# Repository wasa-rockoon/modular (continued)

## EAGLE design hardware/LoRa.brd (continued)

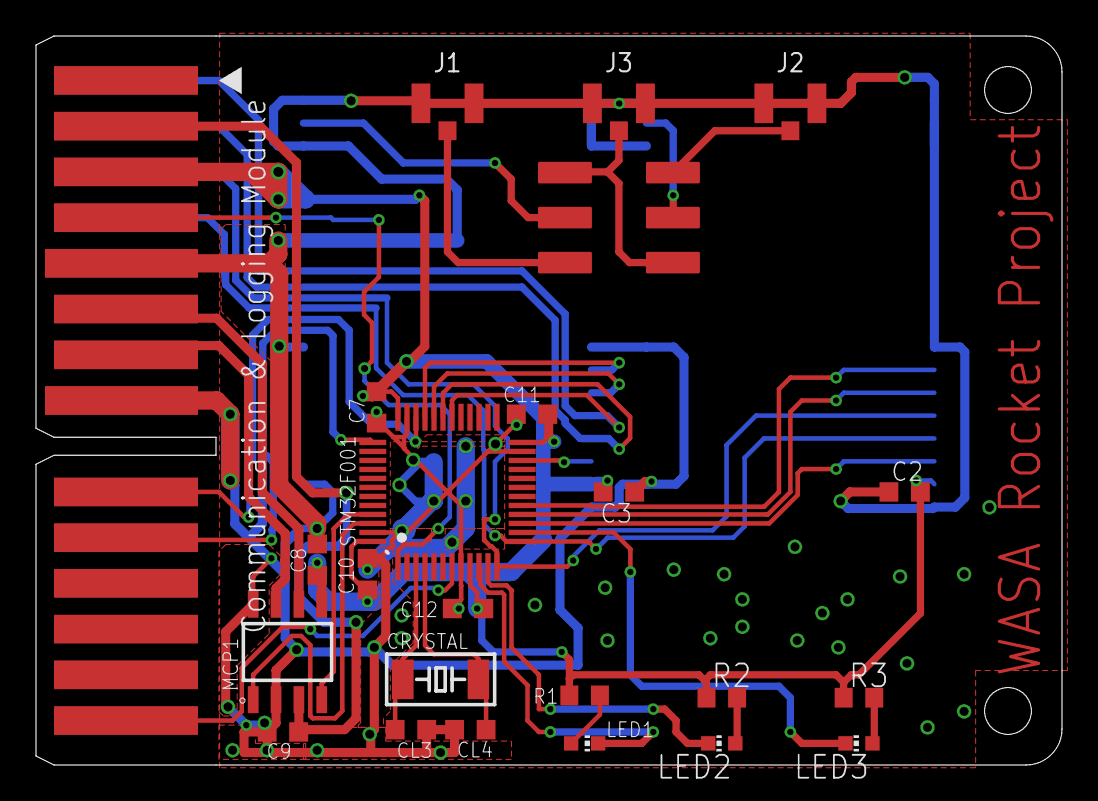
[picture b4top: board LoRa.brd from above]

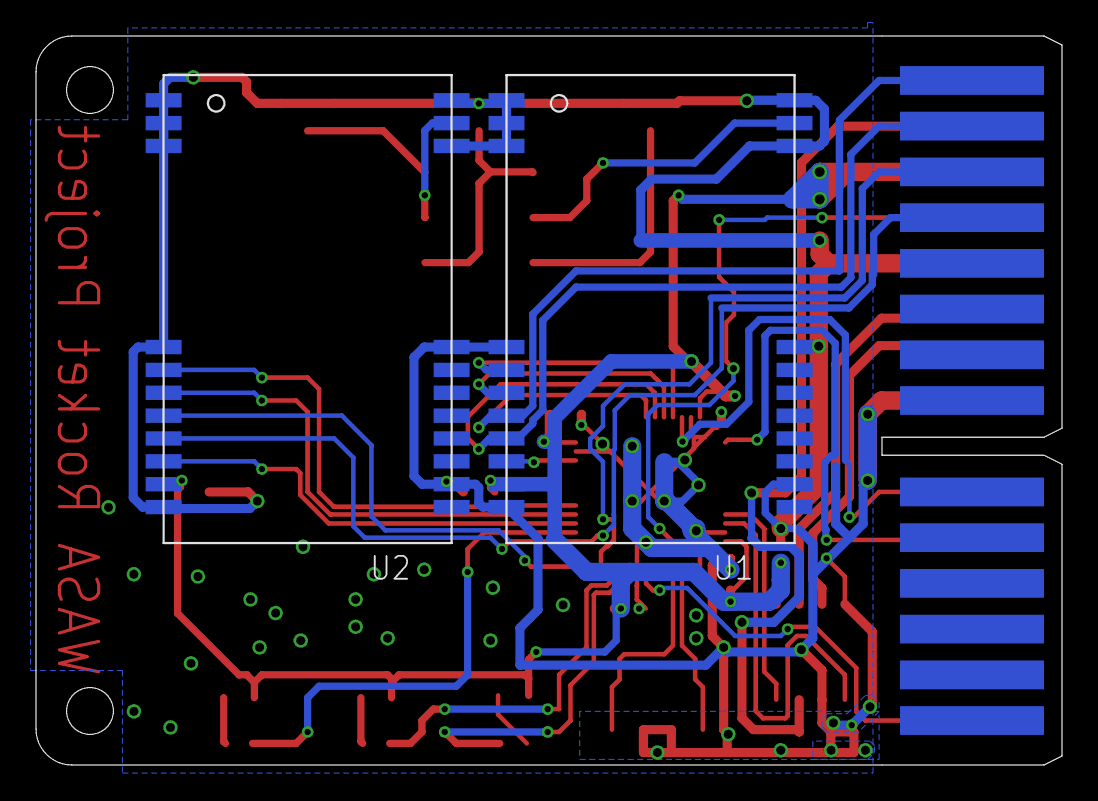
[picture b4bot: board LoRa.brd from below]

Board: 2 copper layers, 57.0 x 40.5 mm, 26 parts (2 on the bottom side), 34 nets.

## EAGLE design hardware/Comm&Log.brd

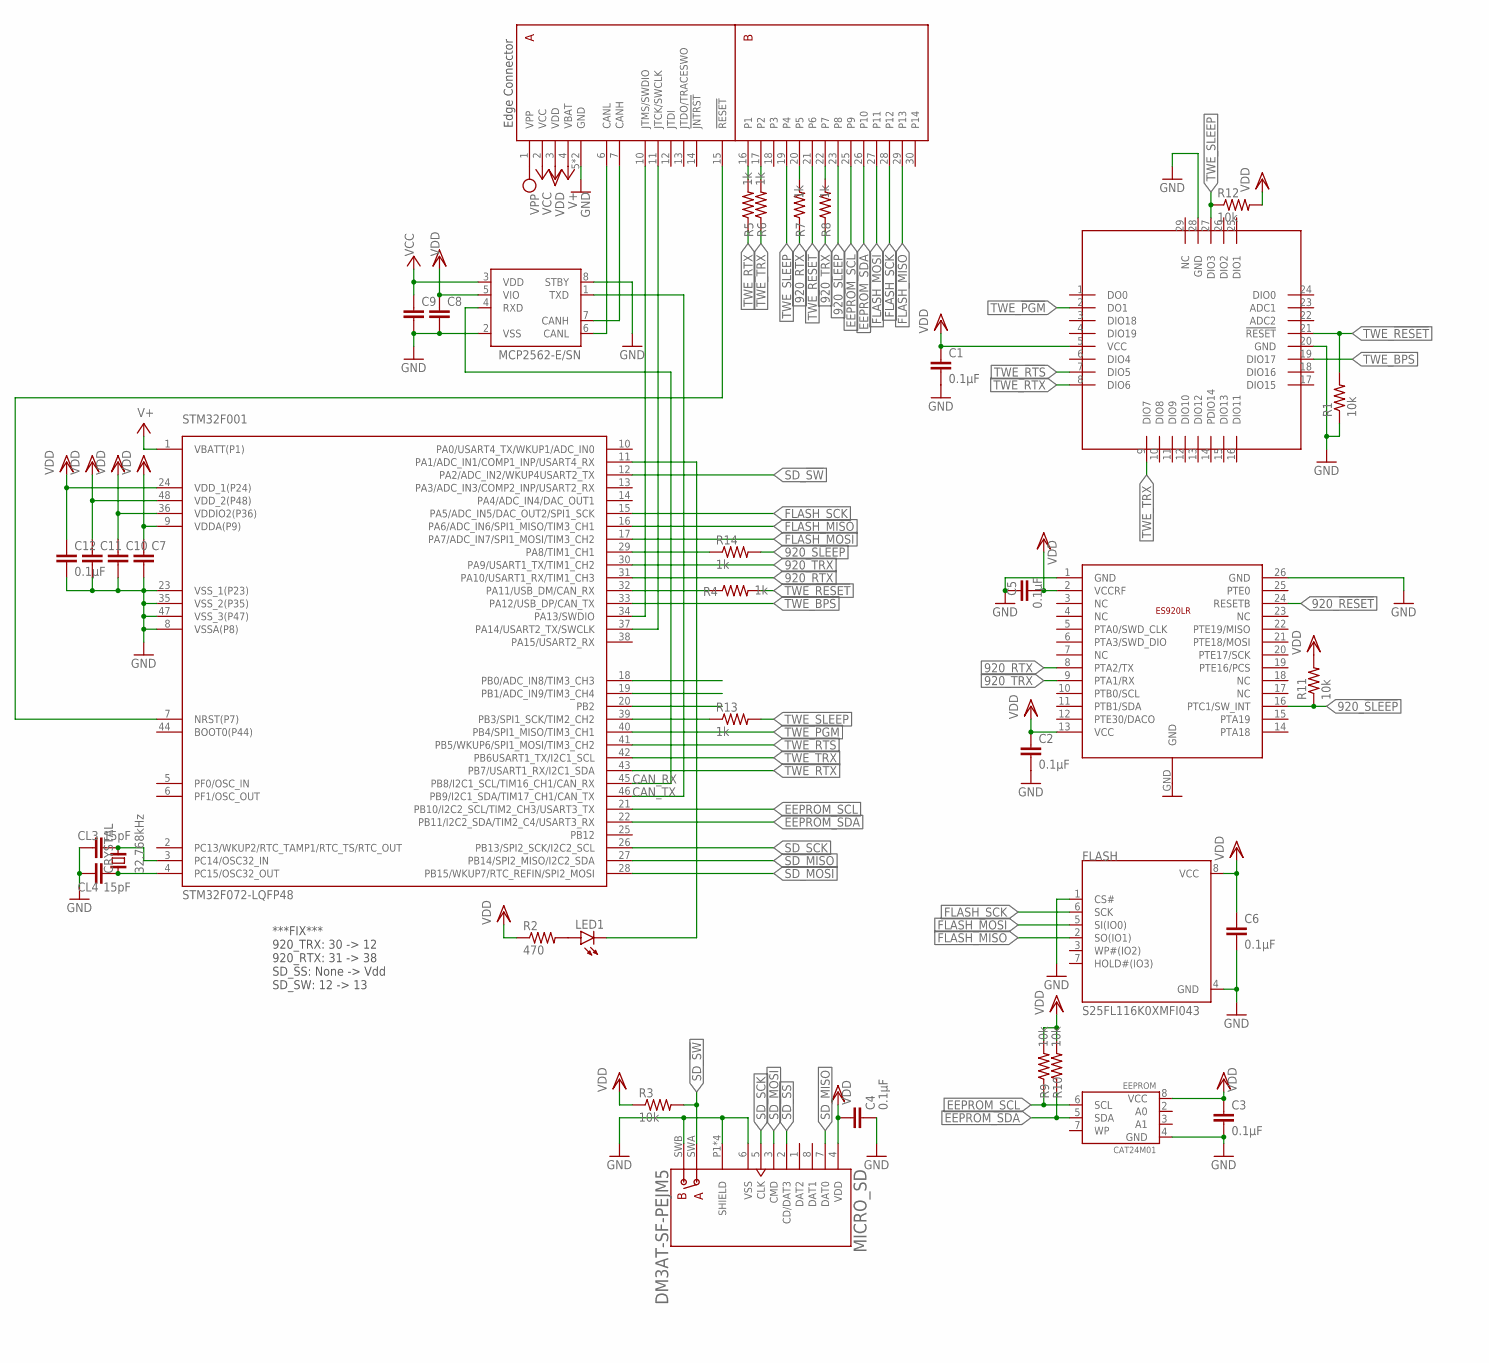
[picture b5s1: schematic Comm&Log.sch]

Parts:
C1, C2, C3, C4, C5, C6, C12: 0.1µF; C0603K
C7, C8, C9, C10, C11: C-EUC0603K; C0603K
CL3, CL4: 15pF; C0603K
CRYSTAL: 32.768kHz; FC-255
EEPROM: CAT24M01; SO-8
ES920LR: ES920LR
FLASH: S25FL116K0XMFI043; SOIC127P600X175-8N
LED1: LEDCHIP-LED0603; CHIP-LED0603
MCP1: MCP2562-E/SN; SOIC127P600X175-8N
MICRO_SD: DM3AT-SF-PEJM5; HRS_DM3AT-SF-PEJM5
R1, R3, R9, R10, R11, R12: 10k; R0603
R2: 470; R0603
R4, R5, R6, R7, R8, R13, R14: 1k; R0603
STM32F001: STM32F072-LQFP48; LQFP48
TWE-LITE: LITE
U$2: EDGE30

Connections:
920_!RESET!: ES920LR.24 (RESETB)
920_!SLEEP!: ES920LR.16 (PTC1/SW_INT), R11.1, R14.2, U$2.23 (P8)
920_!SLEEP!': R14.1, STM32F001.29 (PA8/TIM1_CH1)
920_RTX: ES920LR.8 (PTA2/TX), R7.1, STM32F001.31 (PA10/USART1_RX/TIM1_CH3)
920_RTX_: R7.2, U$2.20 (P5)
920_TRX: ES920LR.9 (PTA1/RX), R8.1, STM32F001.30 (PA9/USART1_TX/TIM1_CH2)
920_TRX_: R8.2, U$2.22 (P7)
CANH1: MCP1.7 (CANH), U$2.7 (CANH)
CANL1: MCP1.6 (CANL), U$2.6 (CANL)
CAN_RX: MCP1.4 (RXD), STM32F001.45 (PB8/I2C1_SCL/TIM16_CH1/CAN_RX)
CAN_TX: MCP1.1 (TXD), STM32F001.46 (PB9/I2C1_SDA/TIM17_CH1/CAN_TX)
EEPROM_SCL: EEPROM.6 (SCL), R9.1, STM32F001.21 (PB10/I2C2_SCL/TIM2_CH3/USART3_TX), U$2.25 (P9)
EEPROM_SDA: EEPROM.5 (SDA), R10.1, STM32F001.22 (PB11/I2C2_SDA/TIM2_C4/USART3_RX), U$2.26 (P10)
FLASH_MISO: FLASH.2 (SO(IO1)), STM32F001.16 (PA6/ADC_IN6/SPI1_MISO/TIM3_CH1), U$2.29 (P13)
FLASH_MOSI: FLASH.5 (SI(IO0)), STM32F001.17 (PA7/ADC_IN7/SPI1_MOSI/TIM3_CH2), U$2.27 (P11)
FLASH_SCK: FLASH.6 (SCK), STM32F001.15 (PA5/ADC_IN5/DAC_OUT2/SPI1_SCK), U$2.28 (P12)
GND: C1.2, C2.2, C3.2, C4.2, C5.1, C6.2, C7.2, C8.2, C9.2, C10.2, C11.2, C12.2, CL3.1, CL4.1, EEPROM.4 (GND), ES920LR.1 (GND), ES920LR.26 (GND), ES920LR.GND, FLASH.1 (CS#), FLASH.4 (GND), MCP1.2 (VSS), MCP1.8 (STBY), MICRO_SD.6 (VSS), MICRO_SD.P1 (SHIELD), MICRO_SD.P2 (SHIELD), MICRO_SD.P3 (SHIELD), MICRO_SD.P4 (SHIELD), MICRO_SD.SWB (B), R1.1, STM32F001.8 (VSSA(P8)), STM32F001.23 (VSS_1(P23)), STM32F001.35 (VSS_2(P35)), STM32F001.47 (VSS_3(P47)), TWE-LITE.20 (GND), TWE-LITE.28 (GND), U$2.5 (GND), U$2.8 (GND)
unnamed: R4.1, STM32F001.32 (PA11/USB_DM/CAN_RX)
unnamed: R6.2, U$2.17 (P2)
unnamed: R13.1, STM32F001.39 (PB3/SPI1_SCK/TIM2_CH2)
unnamed: CL4.2, CRYSTAL.1, STM32F001.4 (PC15/OSC32_OUT)
unnamed: CL3.2, CRYSTAL.2, STM32F001.3 (PC14/OSC32_IN)
unnamed: LED1.C, STM32F001.11 (PA1/ADC_IN1/COMP1_INP/USART4_RX)
unnamed: R5.2, U$2.16 (P1)
unnamed: LED1.A, R2.2
NRST1: STM32F001.7 (NRST(P7)), U$2.15 (!RESET!)
SD_!SS!: MICRO_SD.2 (CD/DAT3)
SD_!SW!: MICRO_SD.SWA (A), R3.2, STM32F001.12 (PA2/ADC_IN2/WKUP4USART2_TX)
SD_MISO: MICRO_SD.7 (DAT0), STM32F001.27 (PB14/SPI2_MISO/I2C2_SDA)
SD_MOSI: MICRO_SD.3 (CMD), STM32F001.28 (PB15/WKUP7/RTC_REFIN/SPI2_MOSI)
SD_SCK: MICRO_SD.5 (CLK), STM32F001.26 (PB13/SPI2_SCK/I2C2_SCL)
SWCLK1: STM32F001.37 (PA14/USART2_TX/SWCLK), U$2.11 (JTCK/SWCLK)
SWDIO1: STM32F001.34 (PA13/SWDIO), U$2.10 (JTMS/SWDIO)
TWE_!PGM!: STM32F001.40 (PB4/SPI1_MISO/TIM3_CH1), TWE-LITE.2 (DO1)
TWE_!RESET!: R1.2, R4.2, TWE-LITE.21 (!RESET!), U$2.21 (P6)
TWE_!RTS!: STM32F001.41 (PB5/WKUP6/SPI1_MOSI/TIM3_CH2), TWE-LITE.7 (DIO5)
TWE_BPS: STM32F001.33 (PA12/USB_DP/CAN_TX), TWE-LITE.19 (DIO17)
TWE_RTX: R5.1, STM32F001.43 (PB7/USART1_RX/I2C1_SDA), TWE-LITE.8 (DIO6)
TWE_SLEEP: R12.1, R13.2, TWE-LITE.27 (DIO3), U$2.19 (P4)
TWE_TRX: R6.1, STM32F001.42 (PB6USART1_TX/I2C1_SCL), TWE-LITE.9 (DIO7)
VBAT: STM32F001.1 (VBATT(P1)), U$2.4 (VBAT)
VCC: C9.1, MCP1.3 (VDD), U$2.2 (VCC)
VDD: C1.1, C2.1, C3.1, C4.1, C5.2, C6.1, C7.1, C8.1, C10.1, C11.1, C12.1, EEPROM.8 (VCC), ES920LR.2 (VCCRF), ES920LR.13 (VCC), FLASH.8 (VCC), MCP1.5 (VIO), MICRO_SD.4 (VDD), R2.1, R3.1, R9.2, R10.2, R11.2, R12.2, STM32F001.9 (VDDA(P9)), STM32F001.24 (VDD_1(P24)), STM32F001.36 (VDDIO2(P36)), STM32F001.48 (VDD_2(P48)), TWE-LITE.5 (VCC), U$2.3 (VDD)
VPP: U$2.1 (VPP)

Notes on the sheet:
***FIX*** 920_TRX: 30 -> 12 920_RTX: 31 -> 38 SD_SS: None -> Vdd SD_SW: 12 -> 13

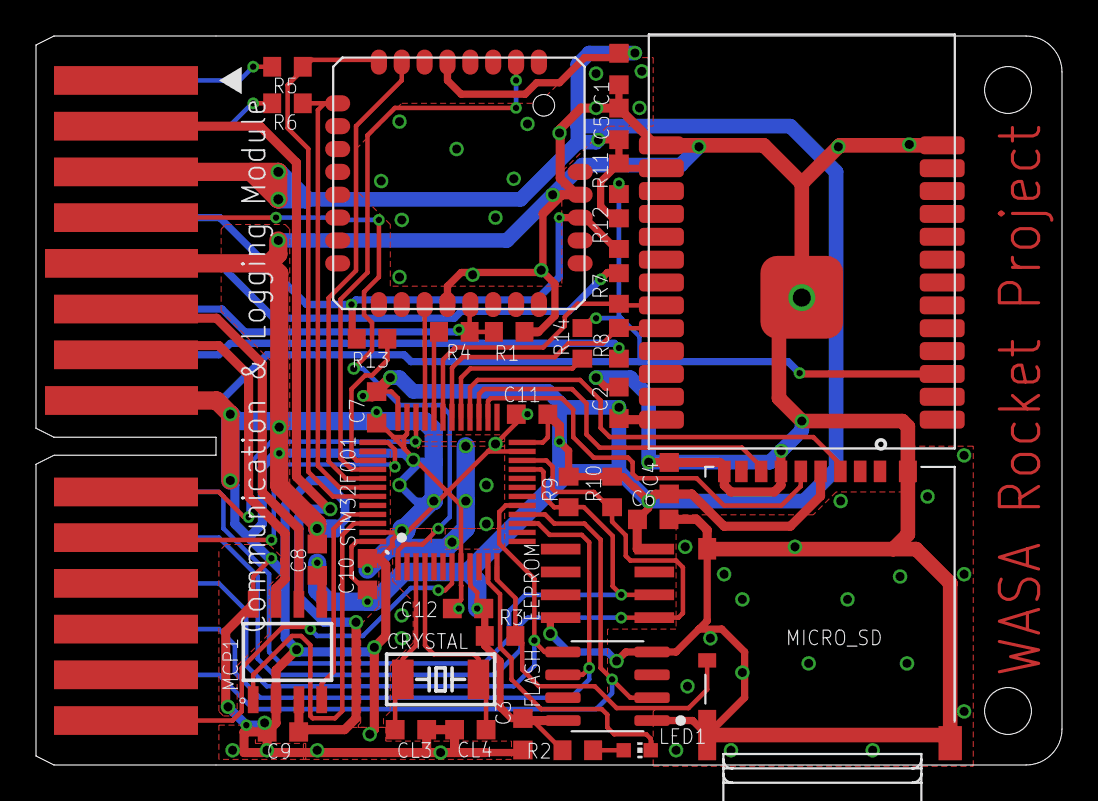
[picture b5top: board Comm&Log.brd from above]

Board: 2 copper layers, 57.0 x 40.5 mm, 38 parts (0 on the bottom side), 41 nets.

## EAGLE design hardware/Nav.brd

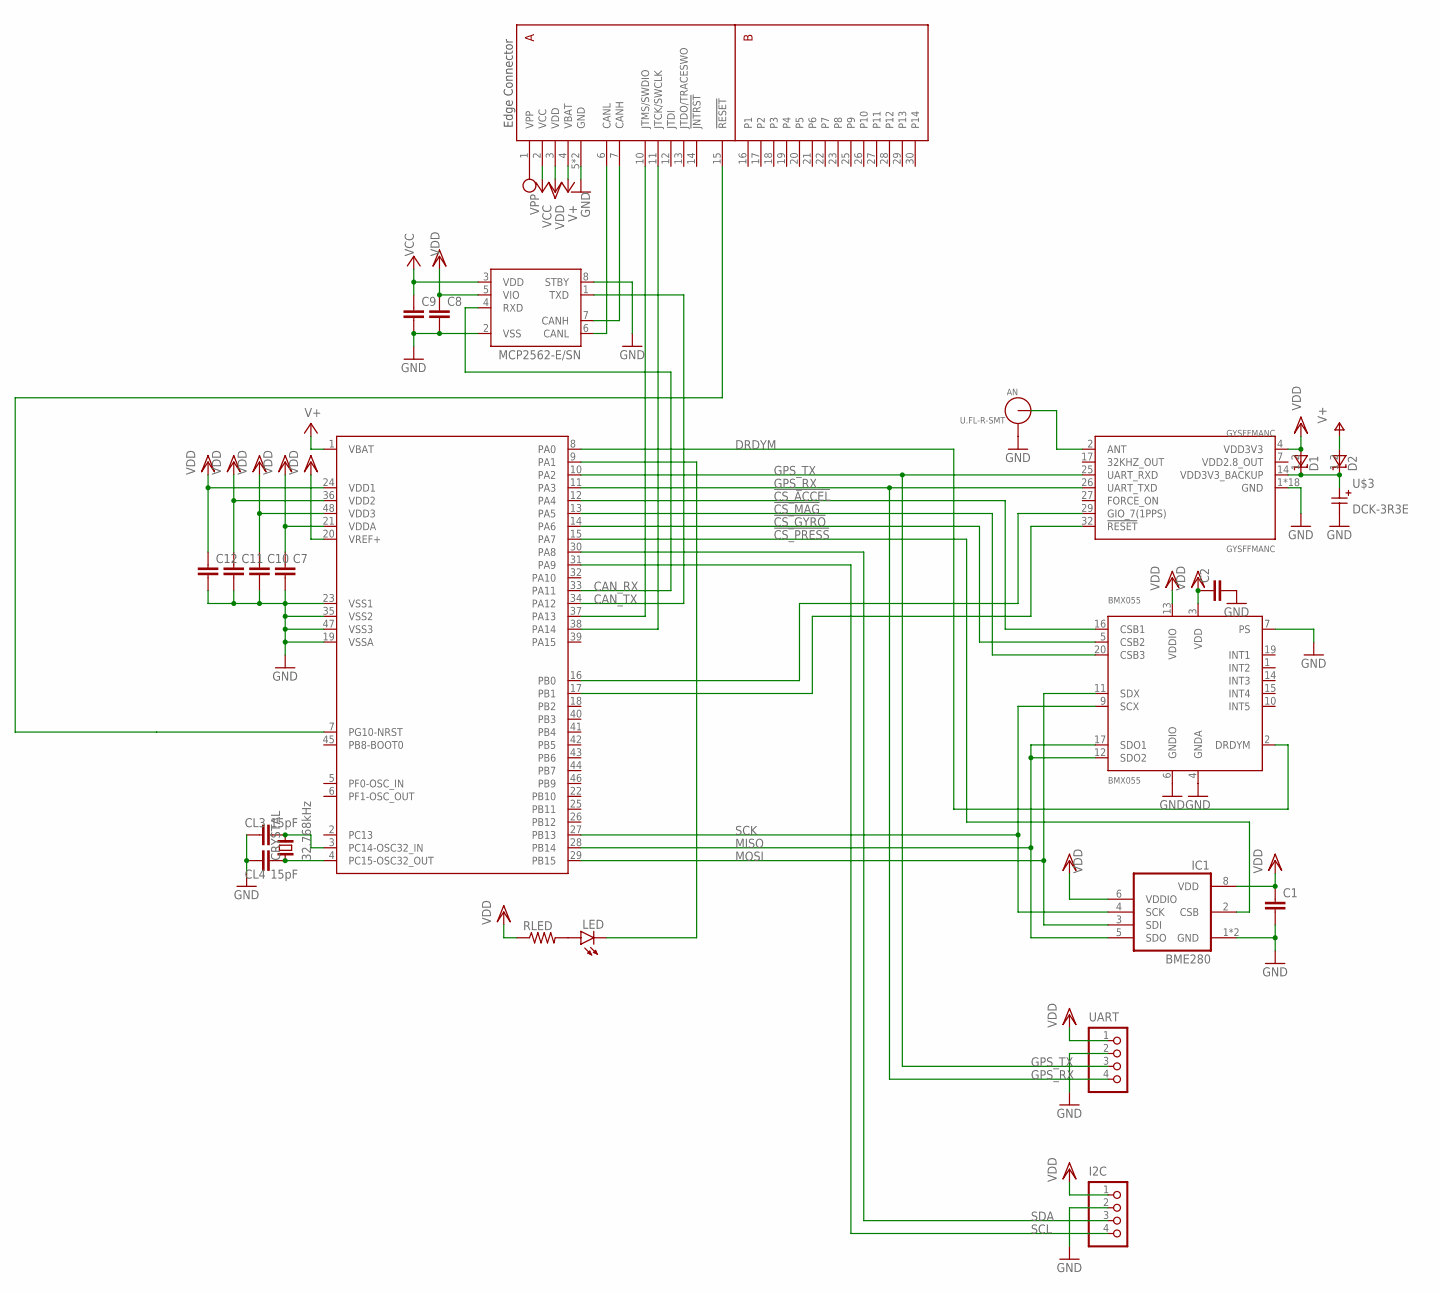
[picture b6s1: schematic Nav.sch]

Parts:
AN: U.FL-R-SMT; U.FL_SMT
BMX055: BMX055
C1, C2, C7, C8, C9, C10, C11, C12: C-EUC0603K; C0603K
CL3, CL4: 15pF; C0603K
CRYSTAL: 32.768kHz; FC-255
D1, D2: RB521S-30TE61; SODFL1608X70N
GYSFFMANC: GYSFFMANC
I2C: S4B-PH-K-S
IC1: BME280
LED: LEDCHIP-LED0603; CHIP-LED0603
MCP2562: MCP2562-E/SN; SOIC127P600X175-8N
RLED: R-US_R0603; R0603
U$1: STM32G431-LQFP48; LQFP48
U$2: EDGE30
U$3: DCK-3R3E; DC,DCK
UART: S4B-PH-K-S

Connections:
!CS_ACCEL!: BMX055.16 (CSB1), U$1.12 (PA4)
!CS_GYRO!: BMX055.5 (CSB2), U$1.14 (PA6)
!CS_MAG!: BMX055.20 (CSB3), U$1.13 (PA5)
!CS_PRESS!: IC1.2 (CSB), U$1.15 (PA7)
CANH1: MCP2562.7 (CANH), U$2.7 (CANH)
CANL1: MCP2562.6 (CANL), U$2.6 (CANL)
CAN_RX: MCP2562.4 (RXD), U$1.33 (PA11)
CAN_TX: MCP2562.1 (TXD), U$1.34 (PA12)
DRDYM: BMX055.2 (DRDYM), U$1.8 (PA0)
GND: AN.GND1, AN.GND2, BMX055.4 (GNDA), BMX055.6 (GNDIO), BMX055.7 (PS), C1.2, C2.2, C7.2, C8.2, C9.2, C10.2, C11.2, C12.2, CL3.1, CL4.1, GYSFFMANC.1 (GND), GYSFFMANC.3 (GND), GYSFFMANC.8 (GND), GYSFFMANC.10 (GND), GYSFFMANC.12 (GND), GYSFFMANC.22 (GND), GYSFFMANC.33 (GND), GYSFFMANC.36 (GND), GYSFFMANC.37 (GND), GYSFFMANC.38 (GND), GYSFFMANC.39 (GND), GYSFFMANC.40 (GND), GYSFFMANC.41 (GND), GYSFFMANC.42 (GND), GYSFFMANC.43 (GND), GYSFFMANC.44 (GND), GYSFFMANC.45 (GND), GYSFFMANC.46 (GND), I2C.2, IC1.1 (GND), IC1.7 (GND), MCP2562.2 (VSS), MCP2562.8 (STBY), U$1.19 (VSSA), U$1.23 (VSS1), U$1.35 (VSS2), U$1.47 (VSS3), U$2.5 (GND), U$2.8 (GND), U$3.-, UART.2
GPS_RX: GYSFFMANC.26 (UART_TXD), U$1.11 (PA3), UART.4
GPS_TX: GYSFFMANC.25 (UART_RXD), U$1.10 (PA2), UART.3
MISO: BMX055.12 (SDO2), BMX055.17 (SDO1), IC1.5 (SDO), U$1.28 (PB14)
MOSI: BMX055.11 (SDX), IC1.3 (SDI), U$1.29 (PB15)
unnamed: AN.SIG (ANT), GYSFFMANC.2 (ANT)
unnamed: GYSFFMANC.29 (GIO_7(1PPS)), U$1.16 (PB0)
unnamed: GYSFFMANC.32 (!RESET!), U$1.17 (PB1)
unnamed: U$1.7 (PG10-NRST), U$2.15 (!RESET!)
unnamed: LED.C, U$1.9 (PA1)
unnamed: CL4.2, CRYSTAL.1, U$1.4 (PC15-OSC32_OUT)
unnamed: CL3.2, CRYSTAL.2, U$1.3 (PC14-OSC32_IN)
unnamed: LED.A, RLED.2
SCK: BMX055.9 (SCX), IC1.4 (SCK), U$1.27 (PB13)
SCL: I2C.4, U$1.31 (PA9)
SDA: I2C.3, U$1.30 (PA8)
SWCLK1: U$1.38 (PA14), U$2.11 (JTCK/SWCLK)
SWDIO1: U$1.37 (PA13), U$2.10 (JTMS/SWDIO)
VBACKUP: D1.1 (K), D2.1 (K), GYSFFMANC.14 (VDD3V3_BACKUP), U$3.+
VBAT: D2.2 (A), U$1.1 (VBAT), U$2.4 (VBAT)
VCC: C9.1, MCP2562.3 (VDD), U$2.2 (VCC)
VDD: BMX055.3 (VDD), BMX055.13 (VDDIO), C1.1, C2.1, C7.1, C8.1, C10.1, C11.1, C12.1, D1.2 (A), GYSFFMANC.4 (VDD3V3), I2C.1, IC1.6 (VDDIO), IC1.8 (VDD), MCP2562.5 (VIO), RLED.1, U$1.20 (VREF+), U$1.21 (VDDA), U$1.24 (VDD1), U$1.36 (VDD2), U$1.48 (VDD3), U$2.3 (VDD), UART.1
VDD2.8_OUT: GYSFFMANC.7 (VDD2.8_OUT)
VPP: U$2.1 (VPP)

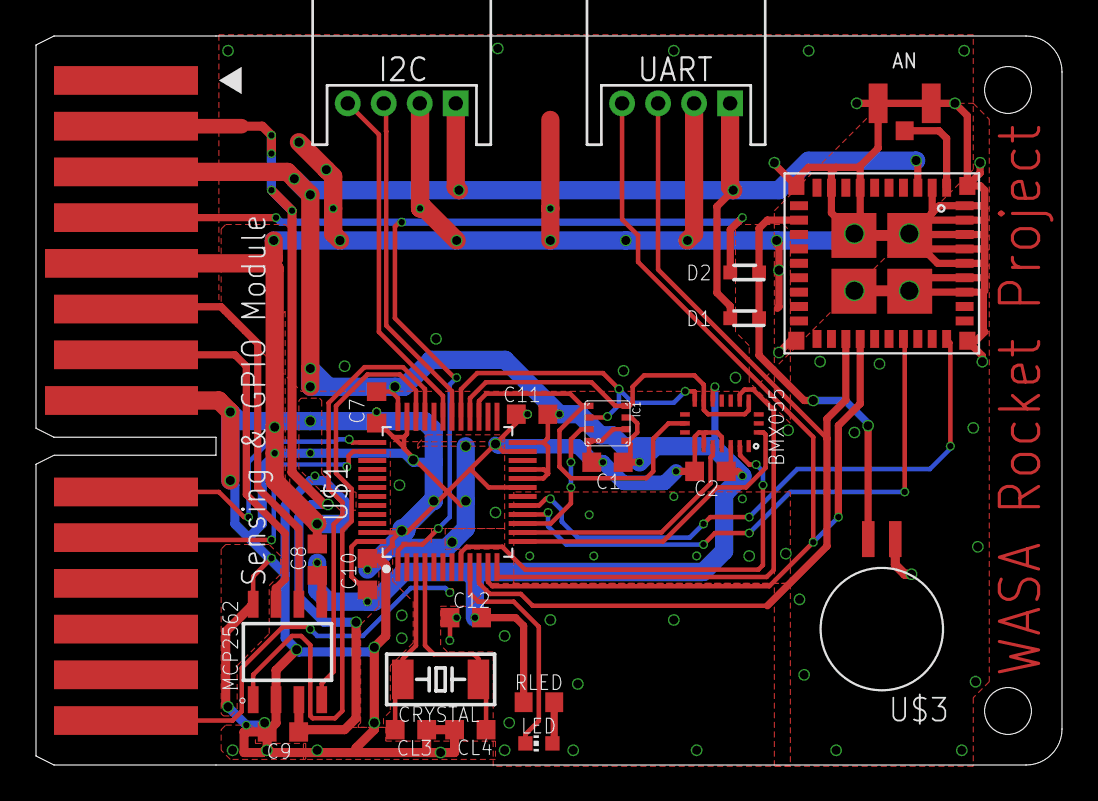
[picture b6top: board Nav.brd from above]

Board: 2 copper layers, 57.0 x 40.5 mm, 25 parts (0 on the bottom side), 31 nets.

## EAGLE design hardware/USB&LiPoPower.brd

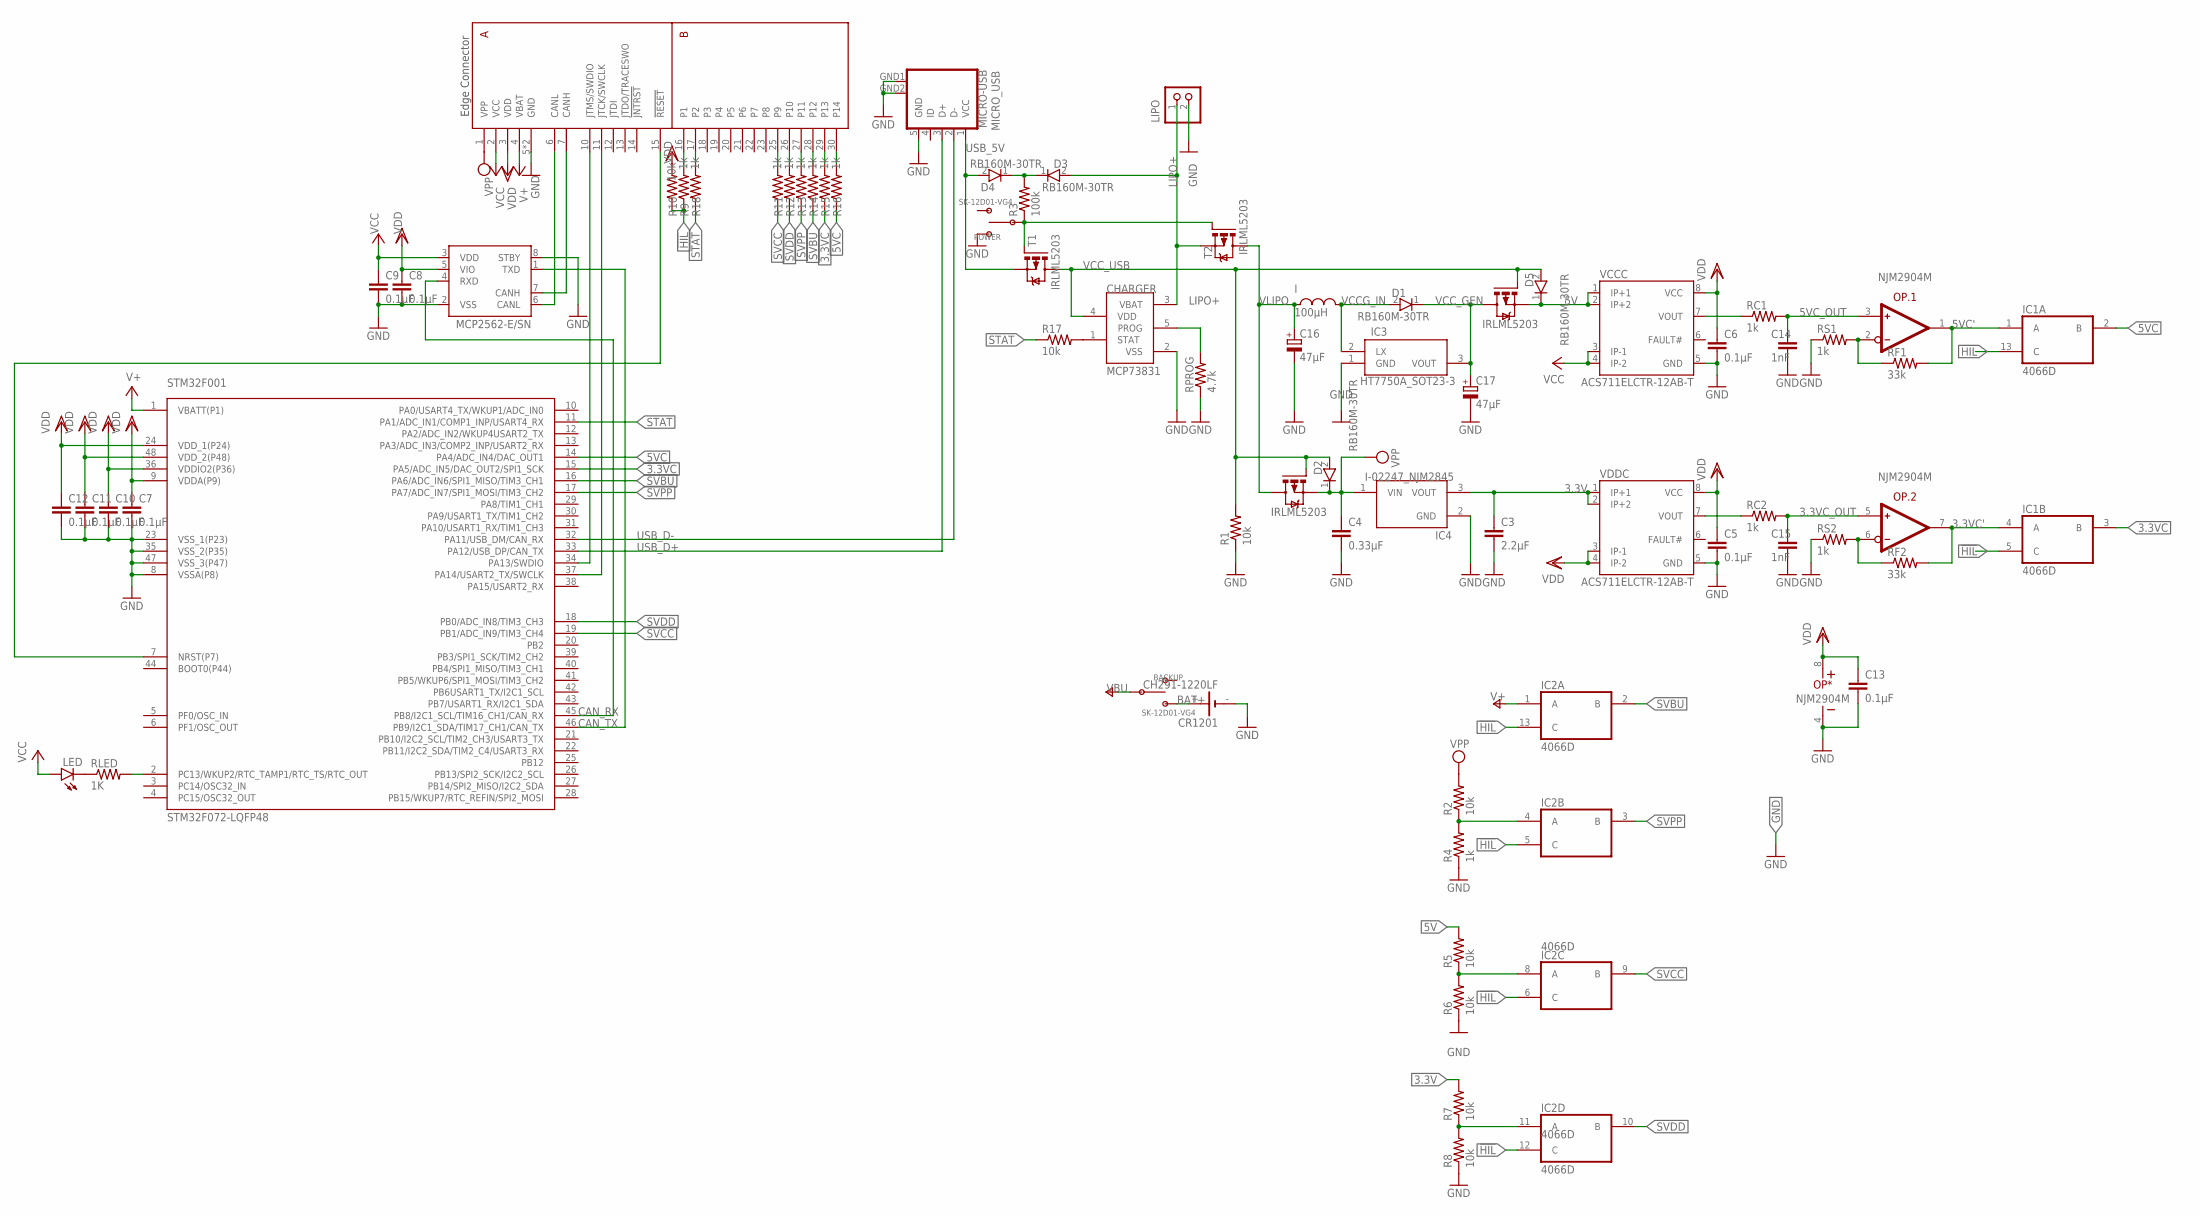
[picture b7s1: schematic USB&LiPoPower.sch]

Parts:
BACKUP: SK-12D01-VG4
C3: 2.2µF; C0603K
C4: 0.33µF; C0603K
C5, C6, C7, C8, C9, C10, C11, C12, C13: 0.1µF; C0603K
C14, C15: 1nF; C0603K
C16, C17: 47µF; UD-5X5,8_NICHICON
CHARGER: MCP73831; SOT23-5L
CR1201: CH291-1220LF
D1, D2, D3, D4, D5: RB160M-30TR; SODFL3516X90N
I: 100µH; NR10050
IC1, IC2: 4066D; SO14
IC3: HT7750A_SOT23-3; SOT95P190X145-3N
IC4: I-02247_NJM2845; TO252
LED: LEDCHIP-LED0603; CHIP-LED0603
LIPO: S2B-PH-K-S
MCP2562: MCP2562-E/SN; SOIC127P600X175-8N
MICRO_USB: MICRO-USB
OP: NJM2904M; SO-8
POWER: SK-12D01-VG4
R1, R2, R5, R6, R7, R8, R10, R17: 10k; R0603
R3: 100k; R0603
R4, R9, R11, R12, R13, R14, R15, R16, R18: 1k; R0603
RC1, RC2: 1k; R0603
RF1, RF2: 33k; R0603
RLED: 1K; R0603
RPROG: 4.7k; R0603
RS1, RS2: 1k; R0603
STM32F001: STM32F072-LQFP48; LQFP48
T1, T2, T3, T4: IRLML5203; MICRO3
U$2: EDGE30
VCCC: ACS711ELCTR-12AB-T; SOIC8
VDDC: ACS711ELCTR-12AB-T; SOIC8

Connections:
3.3V: C3.1, IC4.3 (VOUT), R7.2, VDDC.1 (IP+1), VDDC.2 (IP+2)
3.3VC: IC1.3 (B), R15.1, STM32F001.15 (PA5/ADC_IN5/DAC_OUT2/SPI1_SCK)
3.3VC': IC1.4 (A), OP.7 (OUT), RF2.2
3.3VC_OUT: C15.1, OP.5 (IN+), RC2.2
3.3VC_OUT': RC2.1, VDDC.7 (VOUT)
5V: D5.1 (K), R5.2, T3.2 (S), VCCC.1 (IP+1), VCCC.2 (IP+2)
5VC: IC1.2 (B), R16.1, STM32F001.14 (PA4/ADC_IN4/DAC_OUT1)
5VC': IC1.1 (A), OP.1 (OUT), RF1.2
5VC_OUT: C14.1, OP.3 (IN+), RC1.2
5VC_OUT': RC1.1, VCCC.7 (VOUT)
!HIL!: IC1.5 (C), IC1.13 (C), IC2.5 (C), IC2.6 (C), IC2.12 (C), IC2.13 (C), R9.1, R10.1
BAT+: BACKUP.B, CR1201.+
CANH1: MCP2562.7 (CANH), U$2.7 (CANH)
CANL1: MCP2562.6 (CANL), U$2.6 (CANL)
CAN_RX: MCP2562.4 (RXD), STM32F001.45 (PB8/I2C1_SCL/TIM16_CH1/CAN_RX)
CAN_TX: MCP2562.1 (TXD), STM32F001.46 (PB9/I2C1_SDA/TIM17_CH1/CAN_TX)
GND: C3.2, C4.2, C5.2, C6.2, C7.2, C8.2, C9.2, C10.2, C11.2, C12.2, C13.2, C14.2, C15.2, C16.-, C17.-, CHARGER.2 (VSS), CR1201.-, IC1.7 (VSS), IC2.7 (VSS), IC3.1 (GND), IC4.2 (GND), LIPO.2, MCP2562.2 (VSS), MCP2562.8 (STBY), MICRO_USB.5 (GND), MICRO_USB.GND1 (GND), MICRO_USB.GND2 (GND), OP.4 (V-), POWER.A, R1.1, R4.1, R6.1, R8.1, RPROG.1, RS1.1, RS2.1, STM32F001.8 (VSSA(P8)), STM32F001.23 (VSS_1(P23)), STM32F001.35 (VSS_2(P35)), STM32F001.47 (VSS_3(P47)), U$2.5 (GND), U$2.8 (GND), VCCC.5 (GND), VDDC.5 (GND)
LIPO+: CHARGER.3 (VBAT), D3.2 (A), LIPO.1, T2.2 (S)
unnamed: CHARGER.5 (PROG), RPROG.2
unnamed: CHARGER.1 (STAT), R17.2
unnamed: LED.C, RLED.1
unnamed: OP.2 (IN-), RF1.1, RS1.2
unnamed: OP.6 (IN-), RF2.1, RS2.2
unnamed: POWER.C, R3.1, T1.1 (G), T2.1 (G)
unnamed: D3.1 (K), D4.1 (K), R3.2
unnamed: R16.2, U$2.30 (P14)
unnamed: R15.2, U$2.29 (P13)
unnamed: R14.2, U$2.28 (P12)
unnamed: R13.2, U$2.27 (P11)
unnamed: R12.2, U$2.26 (P10)
unnamed: R11.2, U$2.25 (P9)
unnamed: RLED.2, STM32F001.2 (PC13/WKUP2/RTC_TAMP1/RTC_TS/RTC_OUT)
unnamed: R9.2, U$2.16 (P1)
unnamed: R18.2, U$2.17 (P2)
NRST1: STM32F001.7 (NRST(P7)), U$2.15 (!RESET!)
PVCC: IC2.8 (A), R5.1, R6.2
PVDD: IC2.11 (A), R7.1, R8.2
PVPP: IC2.4 (A), R2.1, R4.2
STAT: R17.1, R18.1, STM32F001.11 (PA1/ADC_IN1/COMP1_INP/USART4_RX)
SVBU: IC2.2 (B), R14.1, STM32F001.16 (PA6/ADC_IN6/SPI1_MISO/TIM3_CH1)
SVCC: IC2.9 (B), R11.1, STM32F001.19 (PB1/ADC_IN9/TIM3_CH4)
SVDD: IC2.10 (B), R12.1, STM32F001.18 (PB0/ADC_IN8/TIM3_CH3)
SVPP: IC2.3 (B), R13.1, STM32F001.17 (PA7/ADC_IN7/SPI1_MOSI/TIM3_CH2)
SWCLK1: STM32F001.37 (PA14/USART2_TX/SWCLK), U$2.11 (JTCK/SWCLK)
SWDIO1: STM32F001.34 (PA13/SWDIO), U$2.10 (JTMS/SWDIO)
USB_5V: D4.2 (A), MICRO_USB.1 (VCC), T1.2 (S)
USB_D+: MICRO_USB.3 (D+), STM32F001.33 (PA12/USB_DP/CAN_TX)
USB_D-: MICRO_USB.2 (D-), STM32F001.32 (PA11/USB_DM/CAN_RX)
VBU: BACKUP.C, IC2.1 (A), STM32F001.1 (VBATT(P1)), U$2.4 (VBAT)
VCC: C9.1, LED.A, MCP2562.3 (VDD), U$2.2 (VCC), VCCC.3 (IP-1), VCCC.4 (IP-2)
VCCG_IN: D1.2 (A), I.2, IC3.2 (LX)
VCC_GEN: C17.+, D1.1 (K), IC3.3 (VOUT), T3.3 (D)
VCC_USB: CHARGER.4 (VDD), D2.2 (A), D5.2 (A), R1.2, T1.3 (D), T3.1 (G), T4.1 (G)
VDD: C5.1, C6.1, C7.1, C8.1, C10.1, C11.1, C12.1, C13.1, IC1.14 (VDD), IC2.14 (VDD), MCP2562.5 (VIO), OP.8 (V+), R10.2, STM32F001.9 (VDDA(P9)), STM32F001.24 (VDD_1(P24)), STM32F001.36 (VDDIO2(P36)), STM32F001.48 (VDD_2(P48)), U$2.3 (VDD), VCCC.8 (VCC), VDDC.3 (IP-1), VDDC.4 (IP-2), VDDC.8 (VCC)
VLIPO: C16.+, I.1, T2.3 (D), T4.3 (D)
VPP: C4.1, D2.1 (K), IC4.1 (VIN), R2.2, T4.2 (S), U$2.1 (VPP)

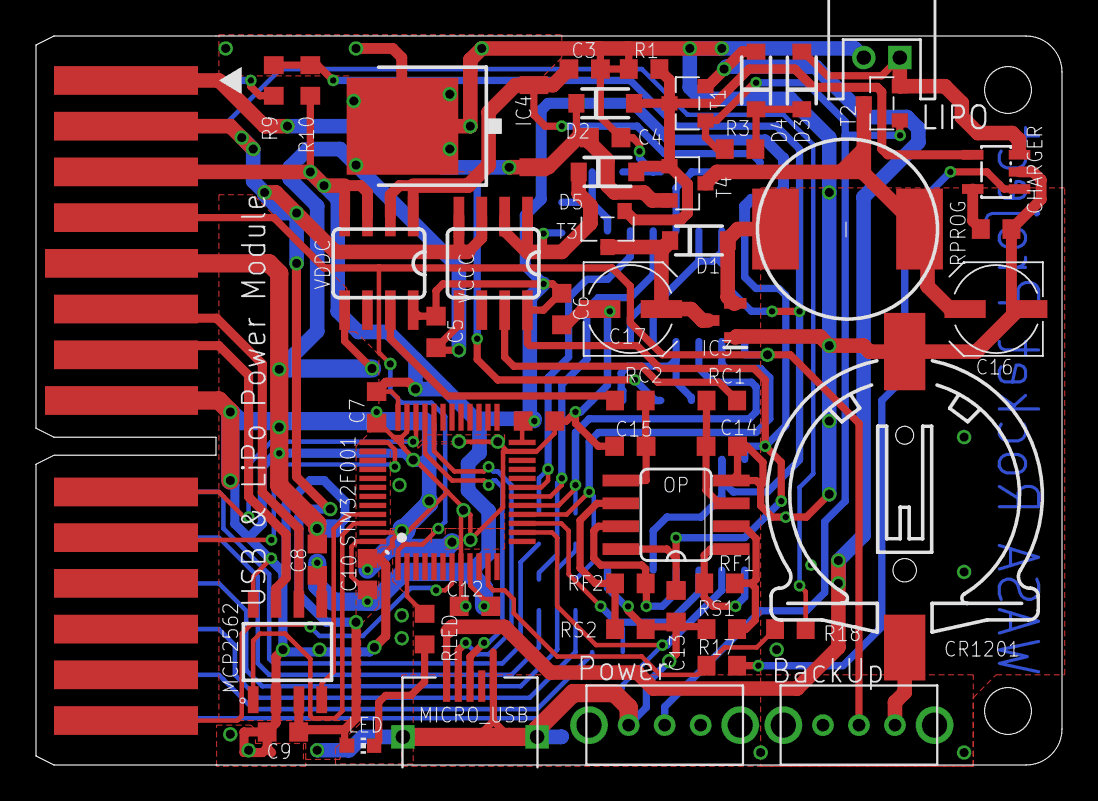
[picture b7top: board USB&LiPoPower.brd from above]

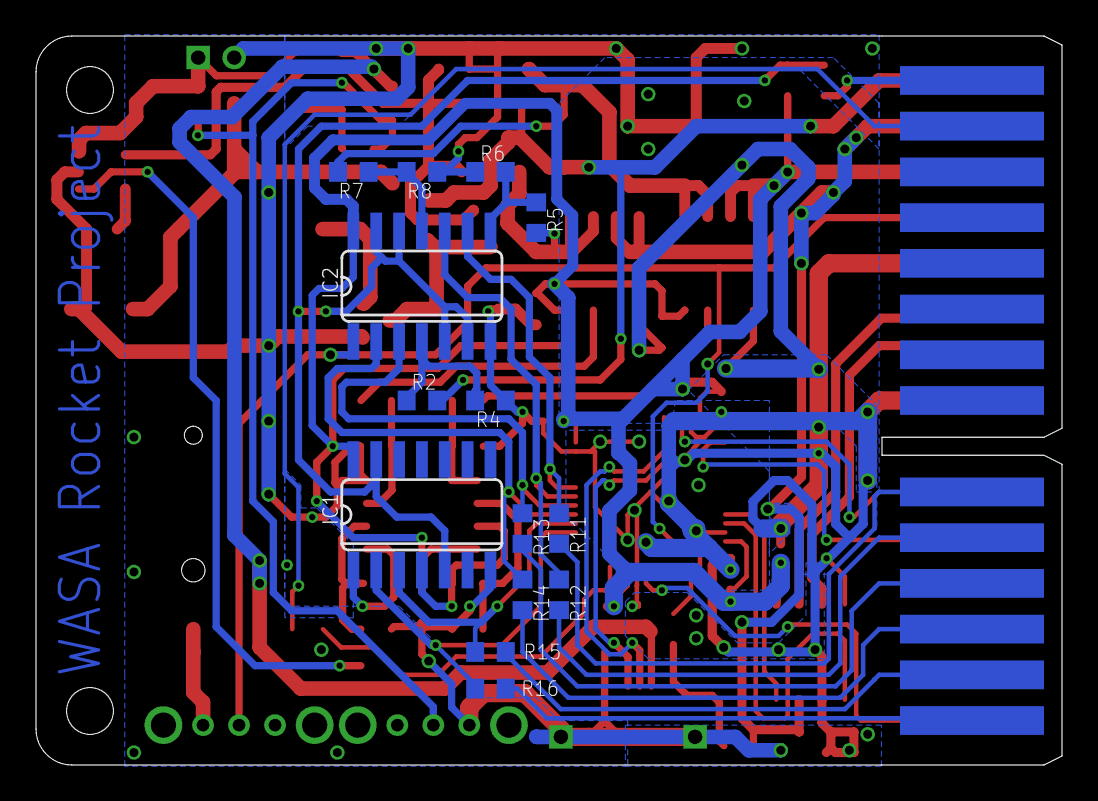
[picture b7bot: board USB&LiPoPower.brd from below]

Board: 2 copper layers, 57.0 x 40.5 mm, 68 parts (14 on the bottom side), 56 nets.
